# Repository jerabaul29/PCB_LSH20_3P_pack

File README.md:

# PCB_LSH20_3P_pack
A PCB for a compact 3P LSH20 pack

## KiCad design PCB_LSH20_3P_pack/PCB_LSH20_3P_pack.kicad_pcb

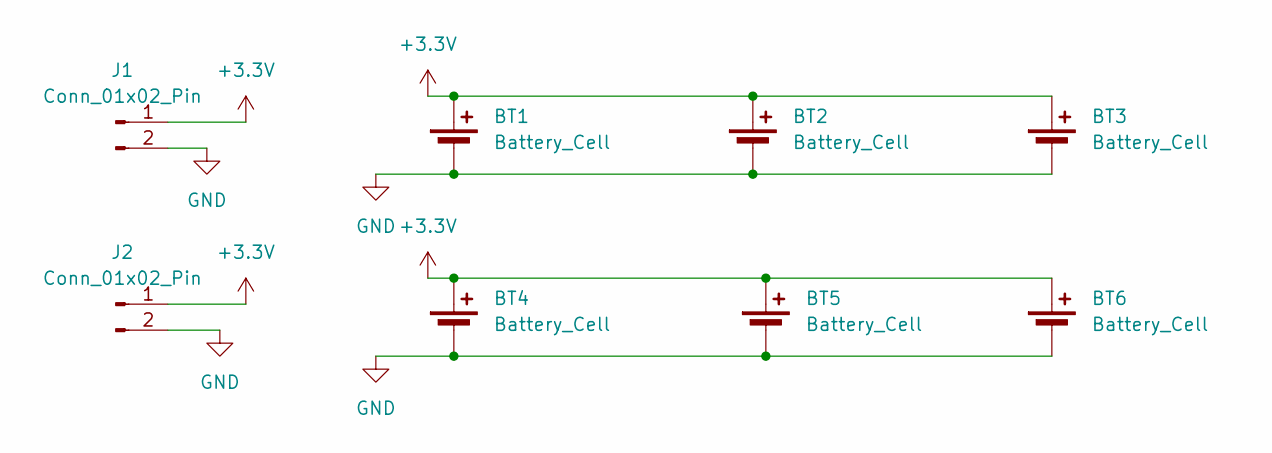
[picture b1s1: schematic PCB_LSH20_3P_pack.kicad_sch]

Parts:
BT1, BT2, BT3, BT4, BT5, BT6: Battery_Cell; lsh20_utags_v1
J1, J2: Conn_01x02_Pin; PinHeader_1x02_P2.54mm_Vertical

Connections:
+3.3V: BT1.1 (+), BT2.1 (+), BT3.1 (+), BT4.1 (+), BT5.1 (+), BT6.1 (+), J1.1, J2.1
GND: BT1.2 (-), BT2.2 (-), BT3.2 (-), BT4.2 (-), BT5.2 (-), BT6.2 (-), J1.2, J2.2

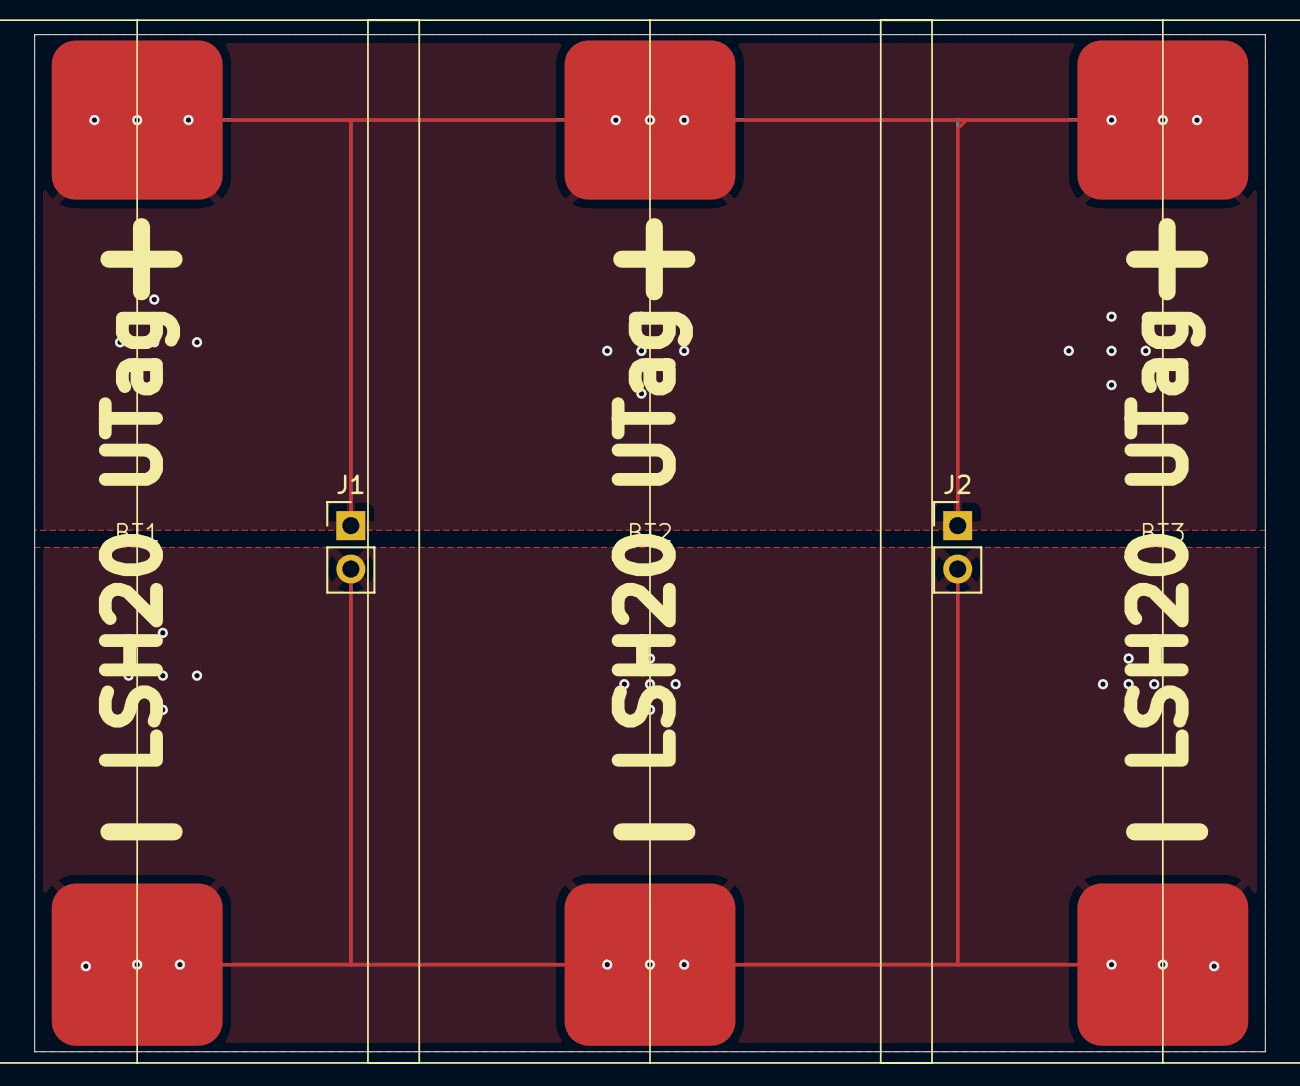
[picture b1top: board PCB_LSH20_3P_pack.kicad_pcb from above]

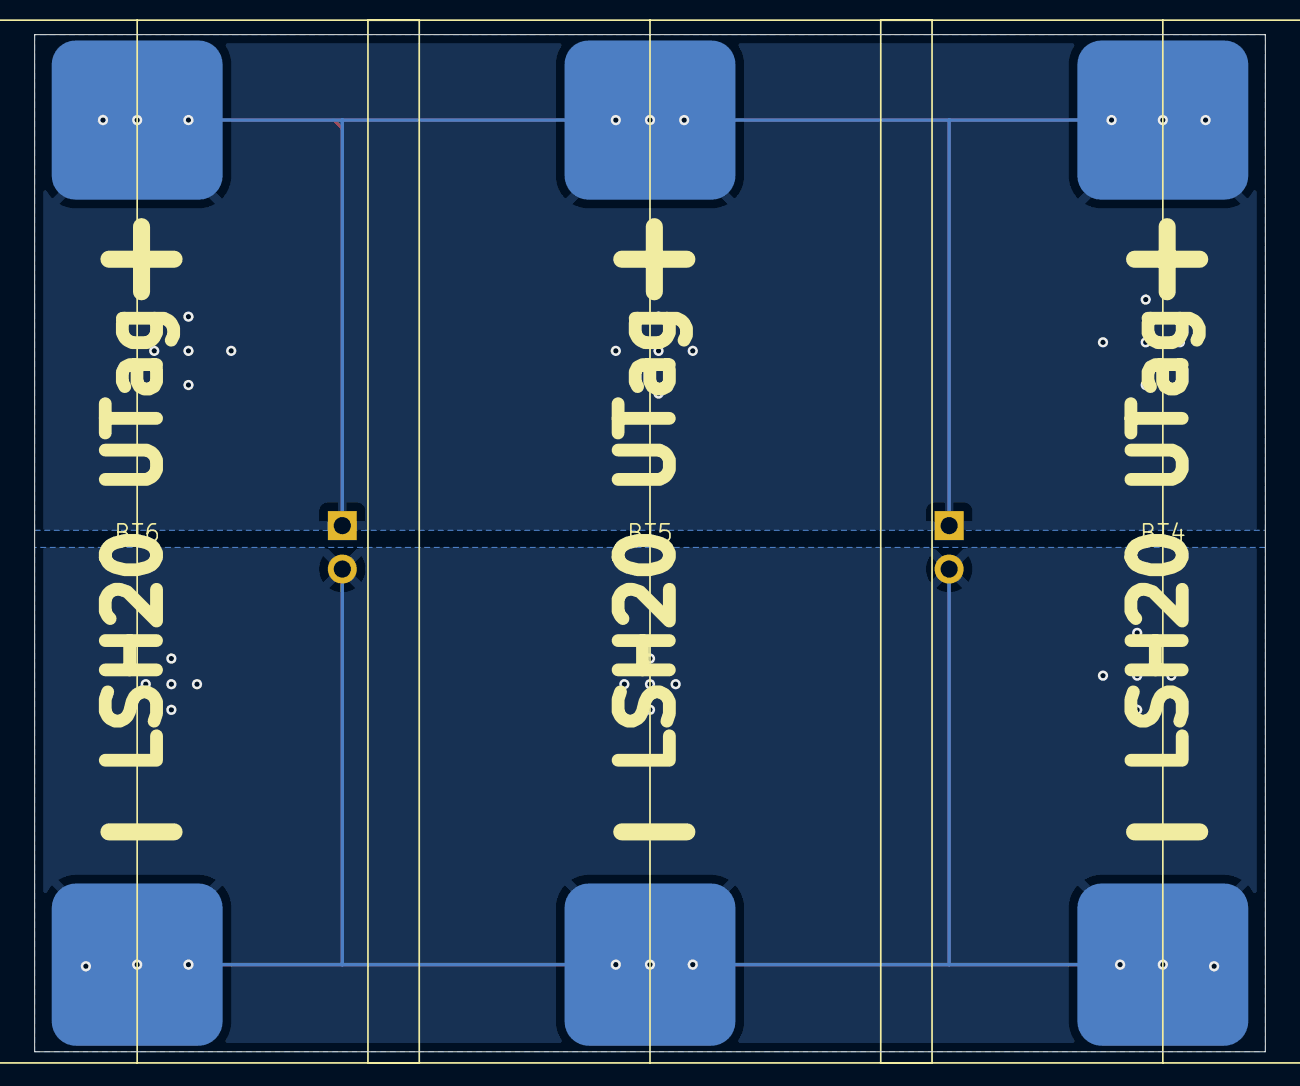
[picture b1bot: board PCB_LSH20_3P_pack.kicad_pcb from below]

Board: 2 copper layers, 72.0 x 59.5 mm, 8 parts (3 on the bottom side), 2 nets.

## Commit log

2026-04-13 WIP start 3 LSH20 PCB
2026-04-13 First production version
